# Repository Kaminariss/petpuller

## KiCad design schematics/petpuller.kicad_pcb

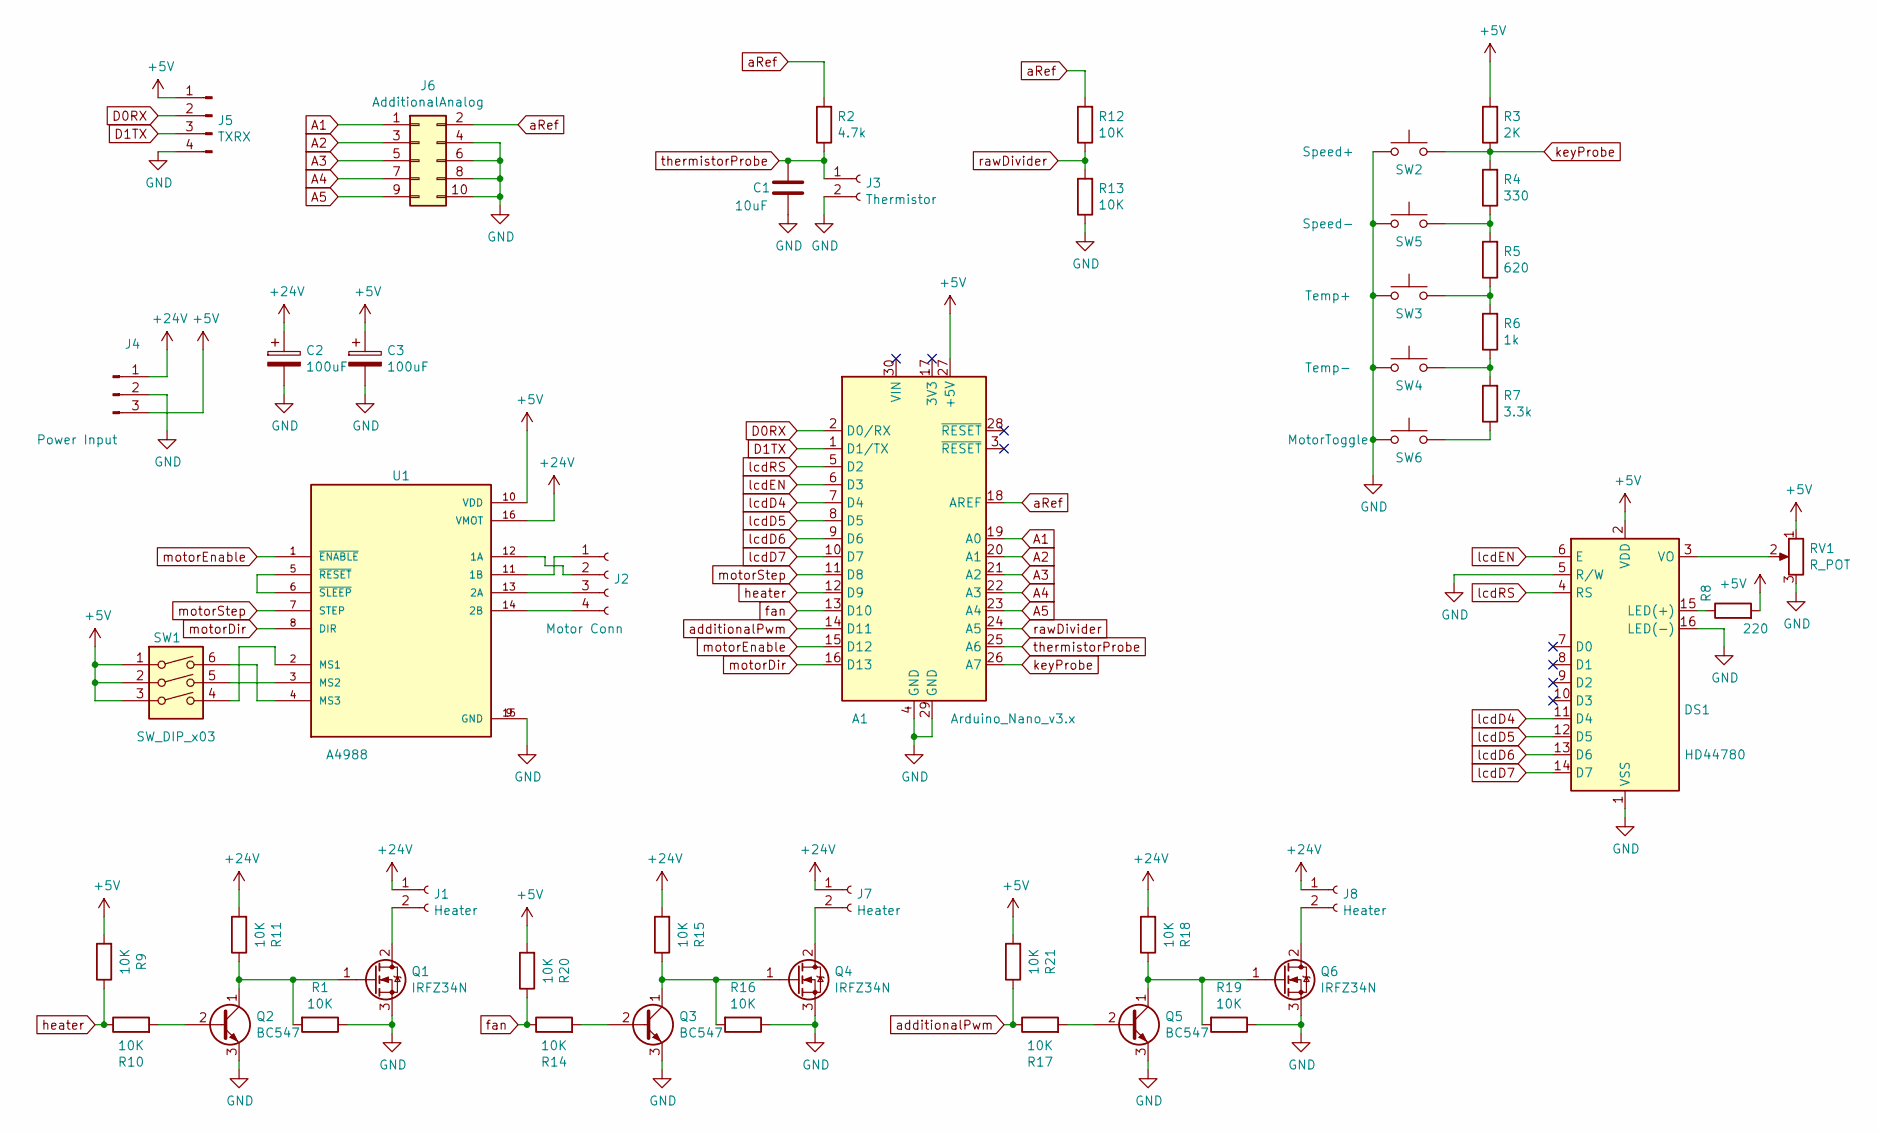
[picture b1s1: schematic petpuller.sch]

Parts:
A1: Arduino_Nano_v3.x; Arduino_Nano
C1: 10uF; CP_Radial_D7.5mm_P2.50mm
C2, C3: 100uF; CP_Radial_D8.0mm_P2.50mm
DS1: HD44780; WC1602A
J1, J7, J8: Heater; TerminalBlock_bornier-2_P5.08mm
J2: Motor Conn; PinHeader_1x04_P2.54mm_Vertical
J3: Thermistor; PinHeader_1x02_P2.54mm_Vertical
J4: Power Input; TerminalBlock_bornier-3_P5.08mm
J5: TXRX; PinHeader_1x04_P2.54mm_Vertical
J6: AdditionalAnalog; PinHeader_2x05_P2.54mm_Vertical
Q1, Q4, Q6: IRFZ34N; TO-220-3_Vertical
Q2, Q3, Q5: BC547; TO-92_Inline
R1, R9, R10, R11, R12, R13, R14, R15, R16, R17, R18, R19, R20, R21: 10K; R_0805_2012Metric_Pad1.20x1.40mm_HandSolder
R2: 4.7k; R_0805_2012Metric_Pad1.20x1.40mm_HandSolder
R3: 2K; R_0805_2012Metric_Pad1.20x1.40mm_HandSolder
R4: 330; R_0805_2012Metric_Pad1.20x1.40mm_HandSolder
R5: 620; R_0805_2012Metric_Pad1.20x1.40mm_HandSolder
R6: 1k; R_0805_2012Metric_Pad1.20x1.40mm_HandSolder
R7: 3.3k; R_0805_2012Metric_Pad1.20x1.40mm_HandSolder
R8: 220; R_0805_2012Metric_Pad1.20x1.40mm_HandSolder
RV1: R_POT; Potentiometer_ACP_CA14-H2,5_Horizontal
SW1: SW_DIP_x03; SW_DIP_SPSTx03_Slide_9.78x9.8mm_W7.62mm_P2.54mm
SW2: Speed+; SW_PUSH-12mm
SW3: Temp+; SW_PUSH-12mm
SW4: Temp-; SW_PUSH-12mm
SW5: Speed-; SW_PUSH-12mm
SW6: MotorToggle; SW_PUSH-12mm
U1: A4988; MODULE_A4988_STEPPER_MOTOR_DRIVER_CARRIER

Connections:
+5V: A1.27 (+5V), C3.1, DS1.2 (VDD), J4.3, J5.1, R3.2, R8.2, R9.2, R20.2, R21.2, RV1.1, SW1.1, SW1.2, SW1.3, U1.10 (VDD)
+24V: C2.1, J1.1, J4.1, J7.1, J8.1, R11.2, R15.2, R18.2, U1.16 (VMOT)
A1: A1.19 (A0), J6.1
A2: A1.20 (A1), J6.3
A3: A1.21 (A2), J6.5
A4: A1.22 (A3), J6.7
A5: A1.23 (A4), J6.9
D0RX: A1.2 (D0/RX), J5.2
D1TX: A1.1 (D1/TX), J5.3
GND: A1.4 (GND), A1.29 (GND), C1.2, C2.2, C3.2, DS1.1 (VSS), DS1.5 (R/W), DS1.16 (LED(-)), J3.2, J4.2, J5.4, J6.4, J6.6, J6.8, J6.10, Q1.3 (S), Q2.3 (E), Q3.3 (E), Q4.3 (S), Q5.3 (E), Q6.3 (S), R1.1, R13.1, R16.1, R19.1, RV1.3, SW2.1, SW3.1, SW4.1, SW5.1, SW6.1, U1.9 (GND), U1.15 (GND)
unnamed: DS1.3 (VO), RV1.2
unnamed: DS1.15 (LED(+)), R8.1
unnamed: J1.2, Q1.2 (D)
unnamed: J2.1, U1.11 (1B)
unnamed: J2.2, U1.12 (1A)
unnamed: J2.3, U1.13 (2A)
unnamed: J2.4, U1.14 (2B)
unnamed: J7.2, Q4.2 (D)
unnamed: J8.2, Q6.2 (D)
unnamed: Q1.1 (G), Q2.1 (C), R1.2, R11.1
unnamed: Q2.2 (B), R10.2
unnamed: Q3.1 (C), Q4.1 (G), R15.1, R16.2
unnamed: Q3.2 (B), R14.2
unnamed: Q5.1 (C), Q6.1 (G), R18.1, R19.2
unnamed: Q5.2 (B), R17.2
unnamed: R4.1, R5.2, SW5.2
unnamed: R5.1, R6.2, SW3.2
unnamed: R6.1, R7.2, SW4.2
unnamed: R7.1, SW6.2
unnamed: SW1.4, U1.2 (MS1)
unnamed: SW1.5, U1.3 (MS2)
unnamed: SW1.6, U1.4 (MS3)
unnamed: U1.5 (~RESET), U1.6 (~SLEEP)
aRef: A1.18 (AREF), J6.2, R2.2, R12.2
additionalPwm: A1.14 (D11), R17.1, R21.1
fan: A1.13 (D10), R14.1, R20.1
heater: A1.12 (D9), R9.1, R10.1
keyProbe: A1.26 (A7), R3.1, R4.2, SW2.2
lcdD4: A1.7 (D4), DS1.11 (D4)
lcdD5: A1.8 (D5), DS1.12 (D5)
lcdD6: A1.9 (D6), DS1.13 (D6)
lcdD7: A1.10 (D7), DS1.14 (D7)
lcdEN: A1.6 (D3), DS1.6 (E)
lcdRS: A1.5 (D2), DS1.4 (RS)
motorDir: A1.16 (D13), U1.8 (DIR)
motorEnable: A1.15 (D12), U1.1 (~ENABLE)
motorStep: A1.11 (D8), U1.7 (STEP)
rawDivider: A1.24 (A5), R12.1, R13.2
thermistorProbe: A1.25 (A6), C1.1, J3.1, R2.1

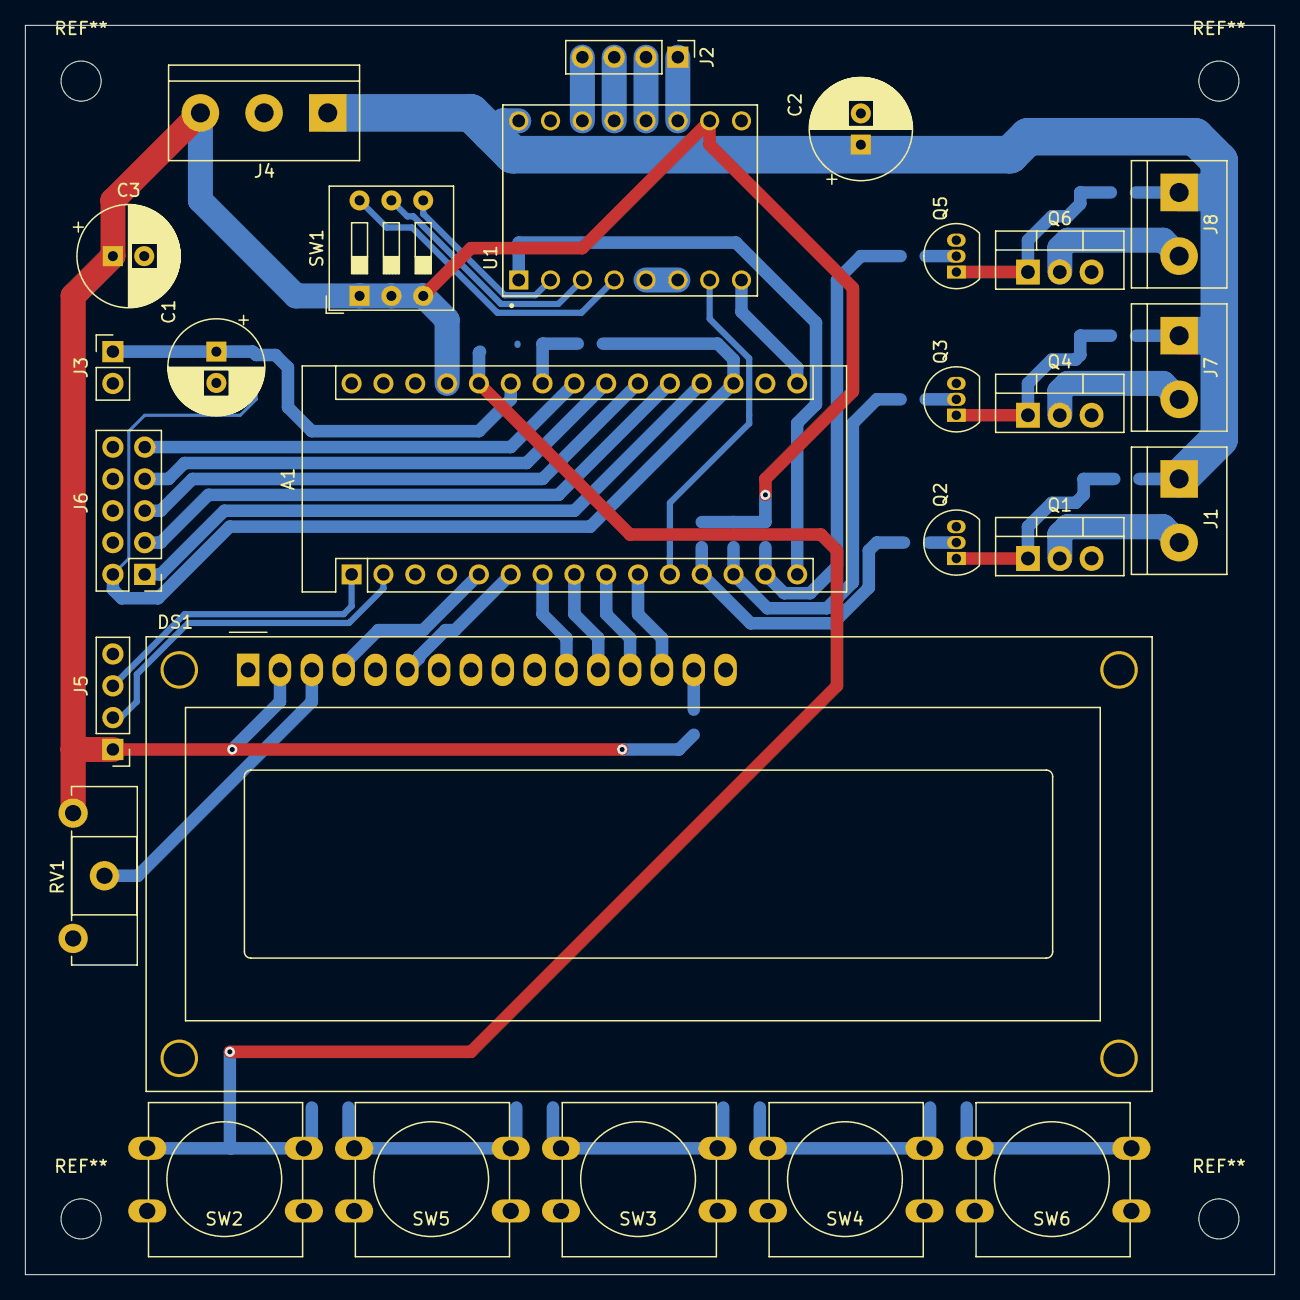
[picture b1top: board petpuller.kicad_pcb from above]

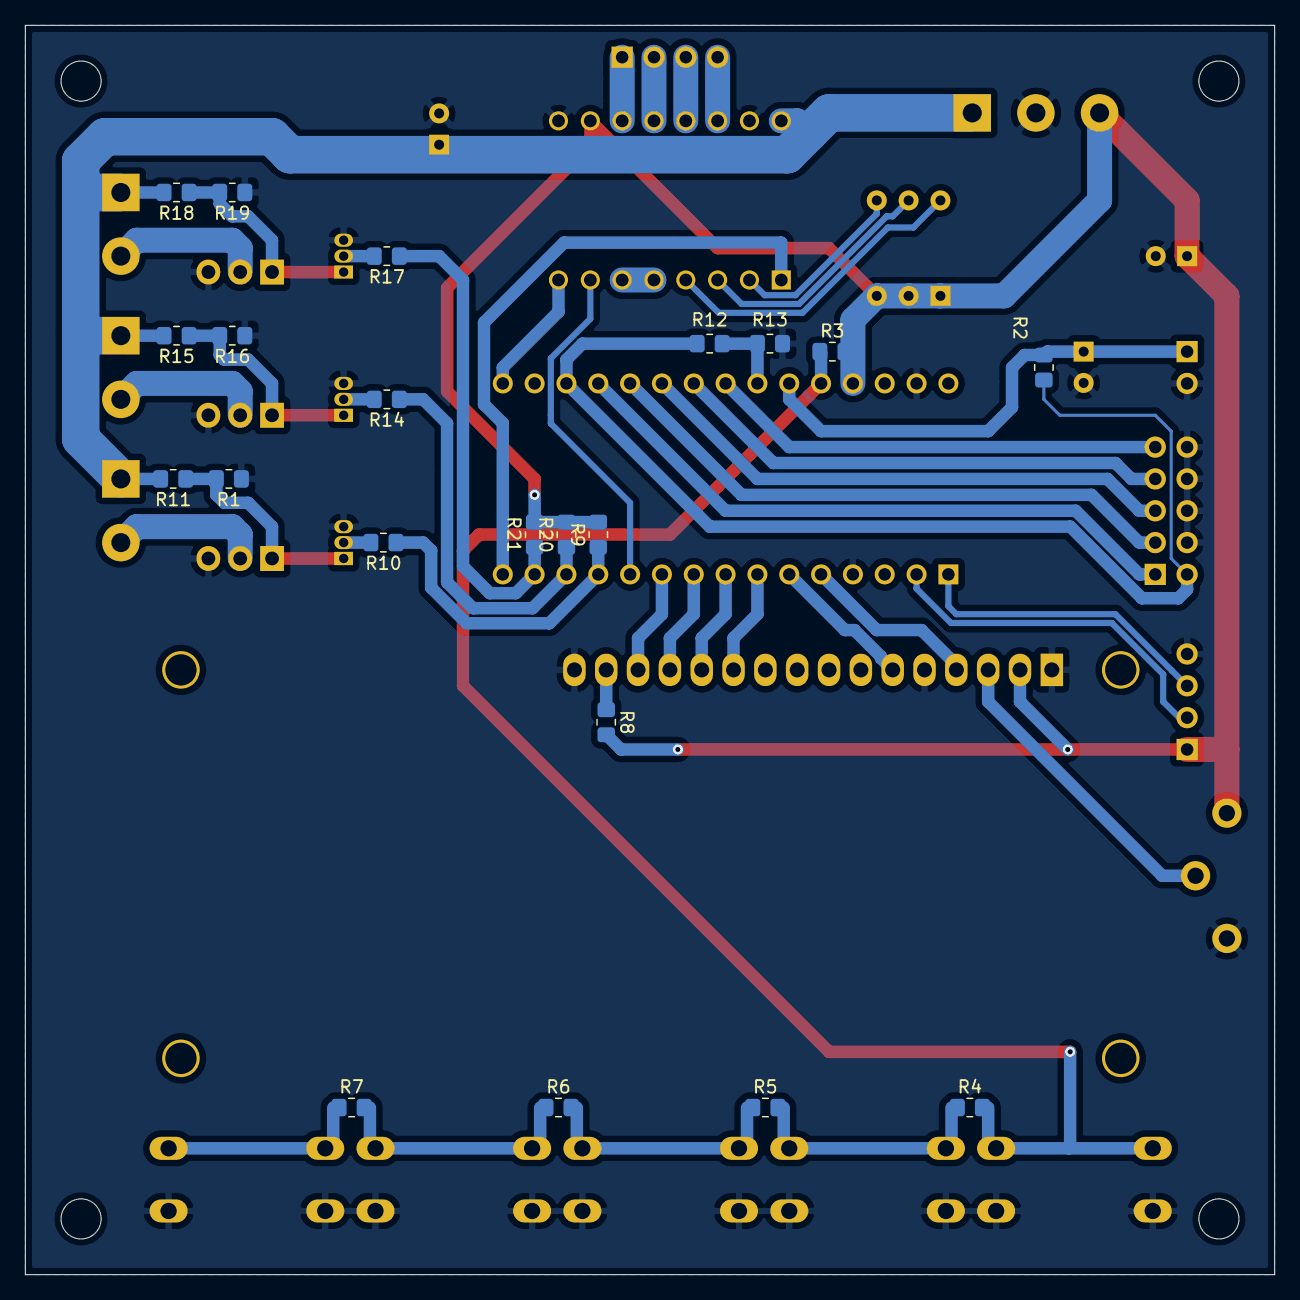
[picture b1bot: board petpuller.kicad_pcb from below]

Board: 2 copper layers, 99.7 x 99.7 mm, 48 parts (21 on the bottom side), 49 nets.

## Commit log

2022-06-17 initial
2022-06-20 median filter for thermistor
2022-07-13 schematic
2022-07-30 board
2022-08-13 fixes
2023-02-01 gerber file updated with the resistors R9, R20 and R21
